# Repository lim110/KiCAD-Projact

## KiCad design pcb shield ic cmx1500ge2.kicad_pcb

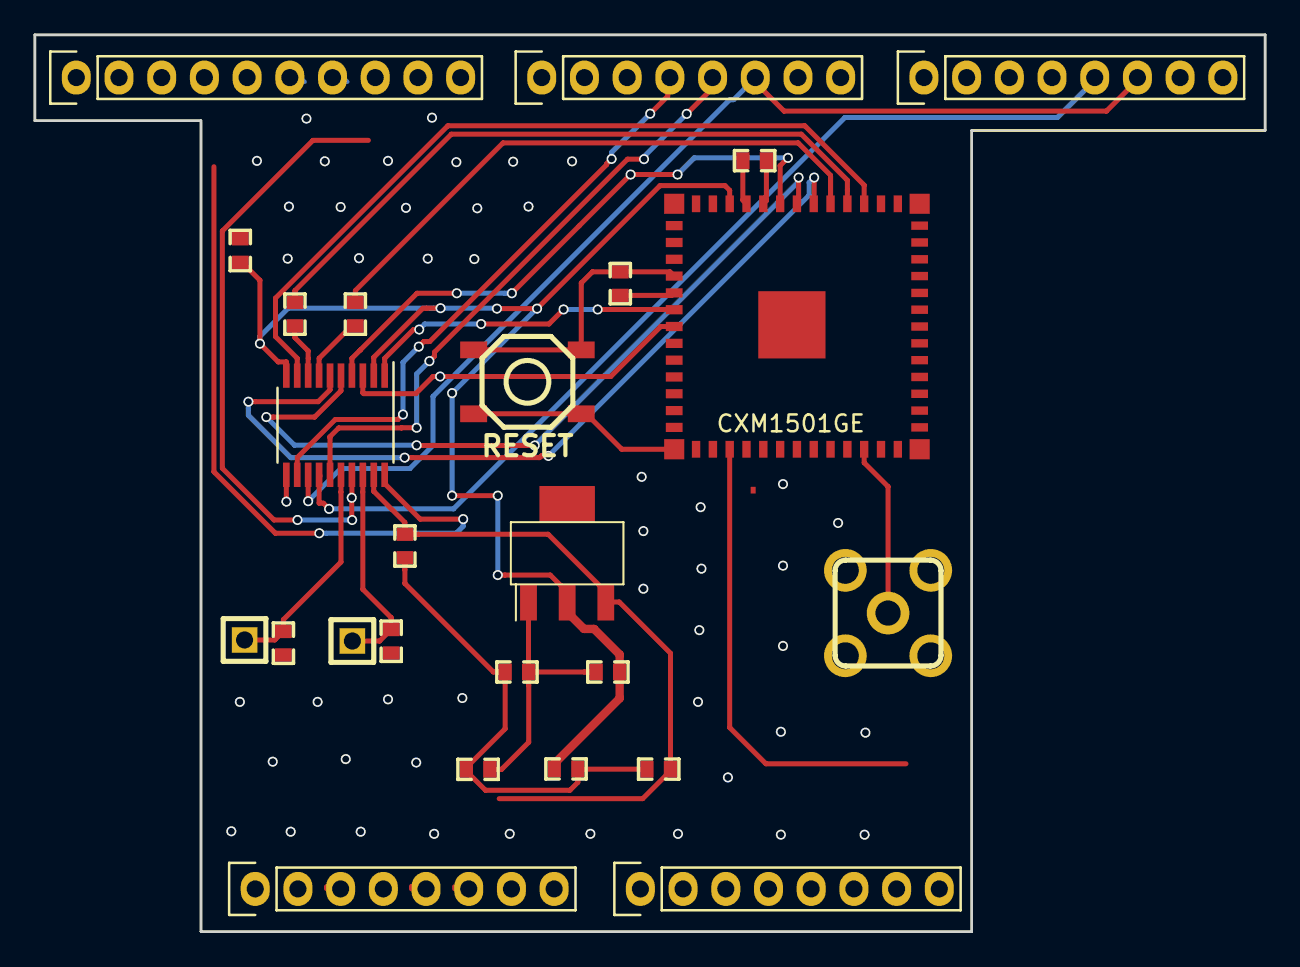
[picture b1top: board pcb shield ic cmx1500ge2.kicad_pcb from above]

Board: 2 copper layers, 73.2 x 53.3 mm, 25 parts (0 on the bottom side), 27 nets.

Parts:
C1, C4: 100uF; C_Ceramic_SMD_0603
C2, C3: 0.1u; C_Ceramic_SMD_0603
C5: 10uf; C_Ceramic_SMD_0603
J1: SMA; SMA_Male_Angled_TH
J3, J4: Conn_01x01_Male; Pin_Header_1x01_Male_10mil_Straight_TH
P1: Power; Socket_Strip_Arduino_1x08
P2: Analog; Socket_Strip_Arduino_1x08
P3: Digital; Socket_Strip_Arduino_1x10
P4: Digital; Socket_Strip_Arduino_1x08
P7: Communication; Socket_Strip_Arduino_1x08
R1: 121; R_Chip_SMD_0603
R2: ?; R_Chip_SMD_0603
R3, R4: RES; R_Chip_SMD_0603
R5, R6: 10; R_Chip_SMD_0603
R7, R8: -; R_Chip_SMD_0603
RESET: BUTTON; Button_4p_W-6.0mm_L-6.0mm_Normal_SMD
U1: CXM1501GE; _CXM1501GE
U2: TXS0108EPW; TSSOP-20_4.4x6.5mm_P0.65mm
U3: LM1117-Adj; TO261AA-LM1117_rev

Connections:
+5V: C3.2, C5.1, P1.5, U2.19, U3.3
/3(**): P4.5, U2.15
/4: P4.4, U2.12
/9(**): P3.9, U2.17
/12(MISO): P3.6, U2.20
/18(Tx1): P7.5, U2.14
/19(Rx1): P4.6, P7.6, U2.13
/+2V: C1.1, C2.2, R1.1, U1.40, U2.2, U2.10, U3.2
/CTS_IC: U1.35, U2.6
/ENB: U1.37, U2.4
/INT_1: U1.36, U2.5
/INT_2: U1.50, U2.3
/RTS_IC: U1.32, U2.9
/RX_IC: R6.2, U1.34
/TX_IC: R5.2, U1.33
/WK_IC: U1.49, U2.1
GND: C1.2, C2.1, C3.1, C4.2, C5.2, J1.2, P1.6, P1.7, P3.4, R2.2, RESET.1, U1.1, U1.2, U1.3, U1.5, U1.6, U1.7, U1.8, U1.9, U1.10, U1.11, U1.13, U1.14, U1.15, U1.16, U1.17, U1.27, U1.28, U1.29, U1.30, U1.31, U1.41, U1.42, U1.43, U1.44, U1.45, U1.46, U1.53, U1.54, U1.55, U1.56, U1.57, U2.11
unnamed: C4.1, R1.2, R2.1, U3.1
unnamed: J1.1, U1.12
unnamed: J3.1, R7.1, U2.18
unnamed: J4.1, R8.1, U2.16
unnamed: R3.2, RESET.2, U1.47
unnamed: R3.1, U1.48
unnamed: R4.1, U1.39
unnamed: R4.2, U1.38
unnamed: R5.1, U2.8
unnamed: R6.1, U2.7

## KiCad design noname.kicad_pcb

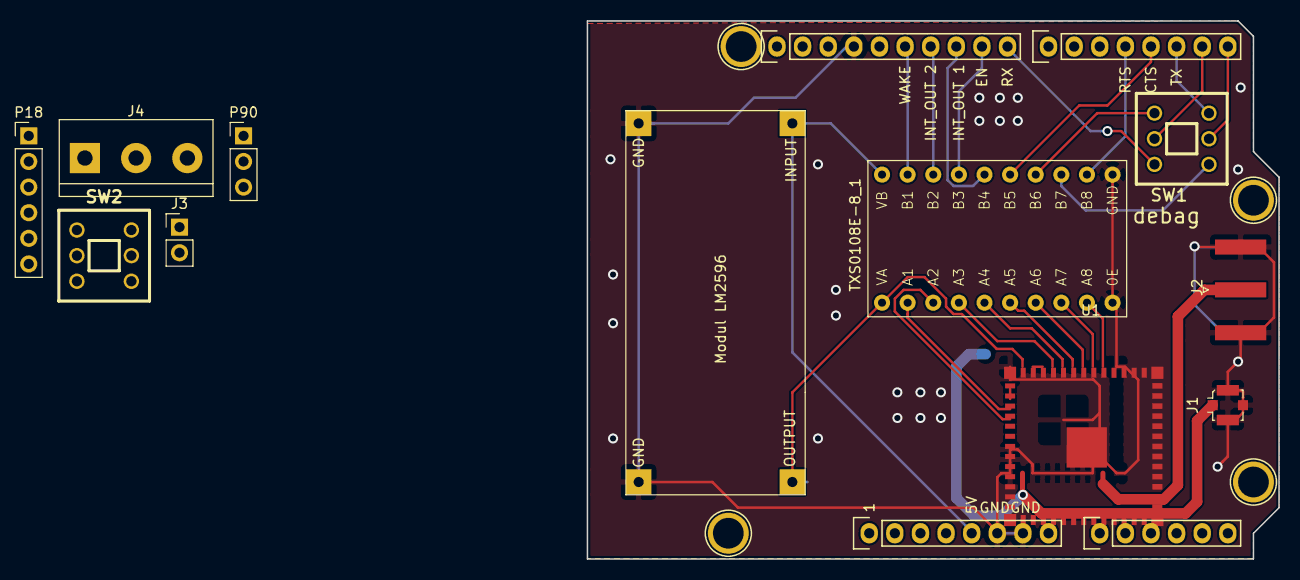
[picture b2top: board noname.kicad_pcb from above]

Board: 2 copper layers, 68.6 x 53.3 mm, 19 parts (0 on the bottom side), 32 nets.

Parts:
J1: SMA; U.FL_Molex_MCRF_73412-0110_Vertical
J2: SMA; SMA_Amphenol_132289_EdgeMount
J3: con_pwr_ardu; PinHeader_1x02_P2.54mm_Vertical
J4: Screw_Terminal_01x03; TerminalBlock_bornier-3_P5.08mm
LM2596_1: modul_dc-dc_lm2596; modul_lvl_dc-dc_lm2596
P1: Power; Socket_Strip_Arduino_1x08
P2: Analog; Socket_Strip_Arduino_1x06
P3: Digital; Socket_Strip_Arduino_1x10
P4: Digital; Socket_Strip_Arduino_1x08
P5, P6, P7, P8: CONN_01X01; Arduino_1pin
P18: PIN FTDI; PinHeader_1x06_P2.54mm_Vertical
P90: Sensor; PinHeader_1x03_P2.54mm_Vertical
SW1, SW2: SWITCH-DPDT; Switch_DPDT_6p_TH
TXS0108E-8_1: modul_lvl-conveter_cjmcu; modul_lvl_conveter_cjmcu
U1: CXM1500GE; _CXM1501GE

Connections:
+5V: J3.1, J4.1, LM2596_1.1, P18.3, P90.3, TXS0108E-8_1.20
/0(Rx): P4.8, SW1.5, SW2.1
/1(Tx): P4.7, SW1.2, SW2.4
/2: P4.6, SW1.4, SW2.6
/3(**): P4.5, TXS0108E-8_1.15
/4: P4.4, TXS0108E-8_1.12
/7: P4.1, P90.2
/8: P3.10, SW1.3, SW2.3
/9(**): P3.9, TXS0108E-8_1.17
/10(**_SS): P3.8, TXS0108E-8_1.16
/11(**_MOSI): P3.7, TXS0108E-8_1.18
/12(MISO): P3.6, TXS0108E-8_1.19
/+2V: LM2596_1.3, TXS0108E-8_1.1, U1.40
/RX: SW1.1, TXS0108E-8_1.14
/RX0: P18.2, SW2.5
/Reset: P1.3, P18.6
/TX: SW1.6, TXS0108E-8_1.13
/TX0: P18.1, SW2.2
GND: J1.2, J2.2, J4.3, LM2596_1.2, LM2596_1.4, P1.6, P1.7, P3.4, P18.4, P18.5, P90.1, TXS0108E-8_1.10, TXS0108E-8_1.11, U1.1, U1.2, U1.3, U1.5, U1.6, U1.7, U1.8, U1.9, U1.10, U1.11, U1.13, U1.14, U1.15, U1.16, U1.17, U1.27, U1.28, U1.29, U1.30, U1.31, U1.41, U1.42, U1.43, U1.44, U1.45, U1.46, U1.53, U1.54, U1.55, U1.56, U1.57
unnamed: J1.1, U1.4
unnamed: J2.1, U1.12
unnamed: J3.2, P1.5
unnamed: TXS0108E-8_1.2, U1.49
unnamed: TXS0108E-8_1.3, U1.50
unnamed: TXS0108E-8_1.4, U1.37
unnamed: TXS0108E-8_1.5, U1.36
unnamed: TXS0108E-8_1.6, U1.35
unnamed: TXS0108E-8_1.7, U1.34
unnamed: TXS0108E-8_1.8, U1.33
unnamed: TXS0108E-8_1.9, U1.32
unnamed: U1.38, U1.39
unnamed: U1.47, U1.48

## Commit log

2019-04-23 pcb sampai pada skematik dan membuat footprint dari komponen-komponen yang diperlukan
2019-04-24 sampai layout pcb
2019-04-24 routing PCB sudah selesai
2019-04-24 penambahan komponen 3d
2019-04-25 penambahan via untuk grounding
2019-04-25 pengubahan komponen dpdt dan perbaikan routing layer pada rf komponen
2019-04-25 mengubah routing pada jalur sinyal rf agar impedasi 50 ohm dan menambah file duplicate print pcb
2019-09-25 Add README.md
